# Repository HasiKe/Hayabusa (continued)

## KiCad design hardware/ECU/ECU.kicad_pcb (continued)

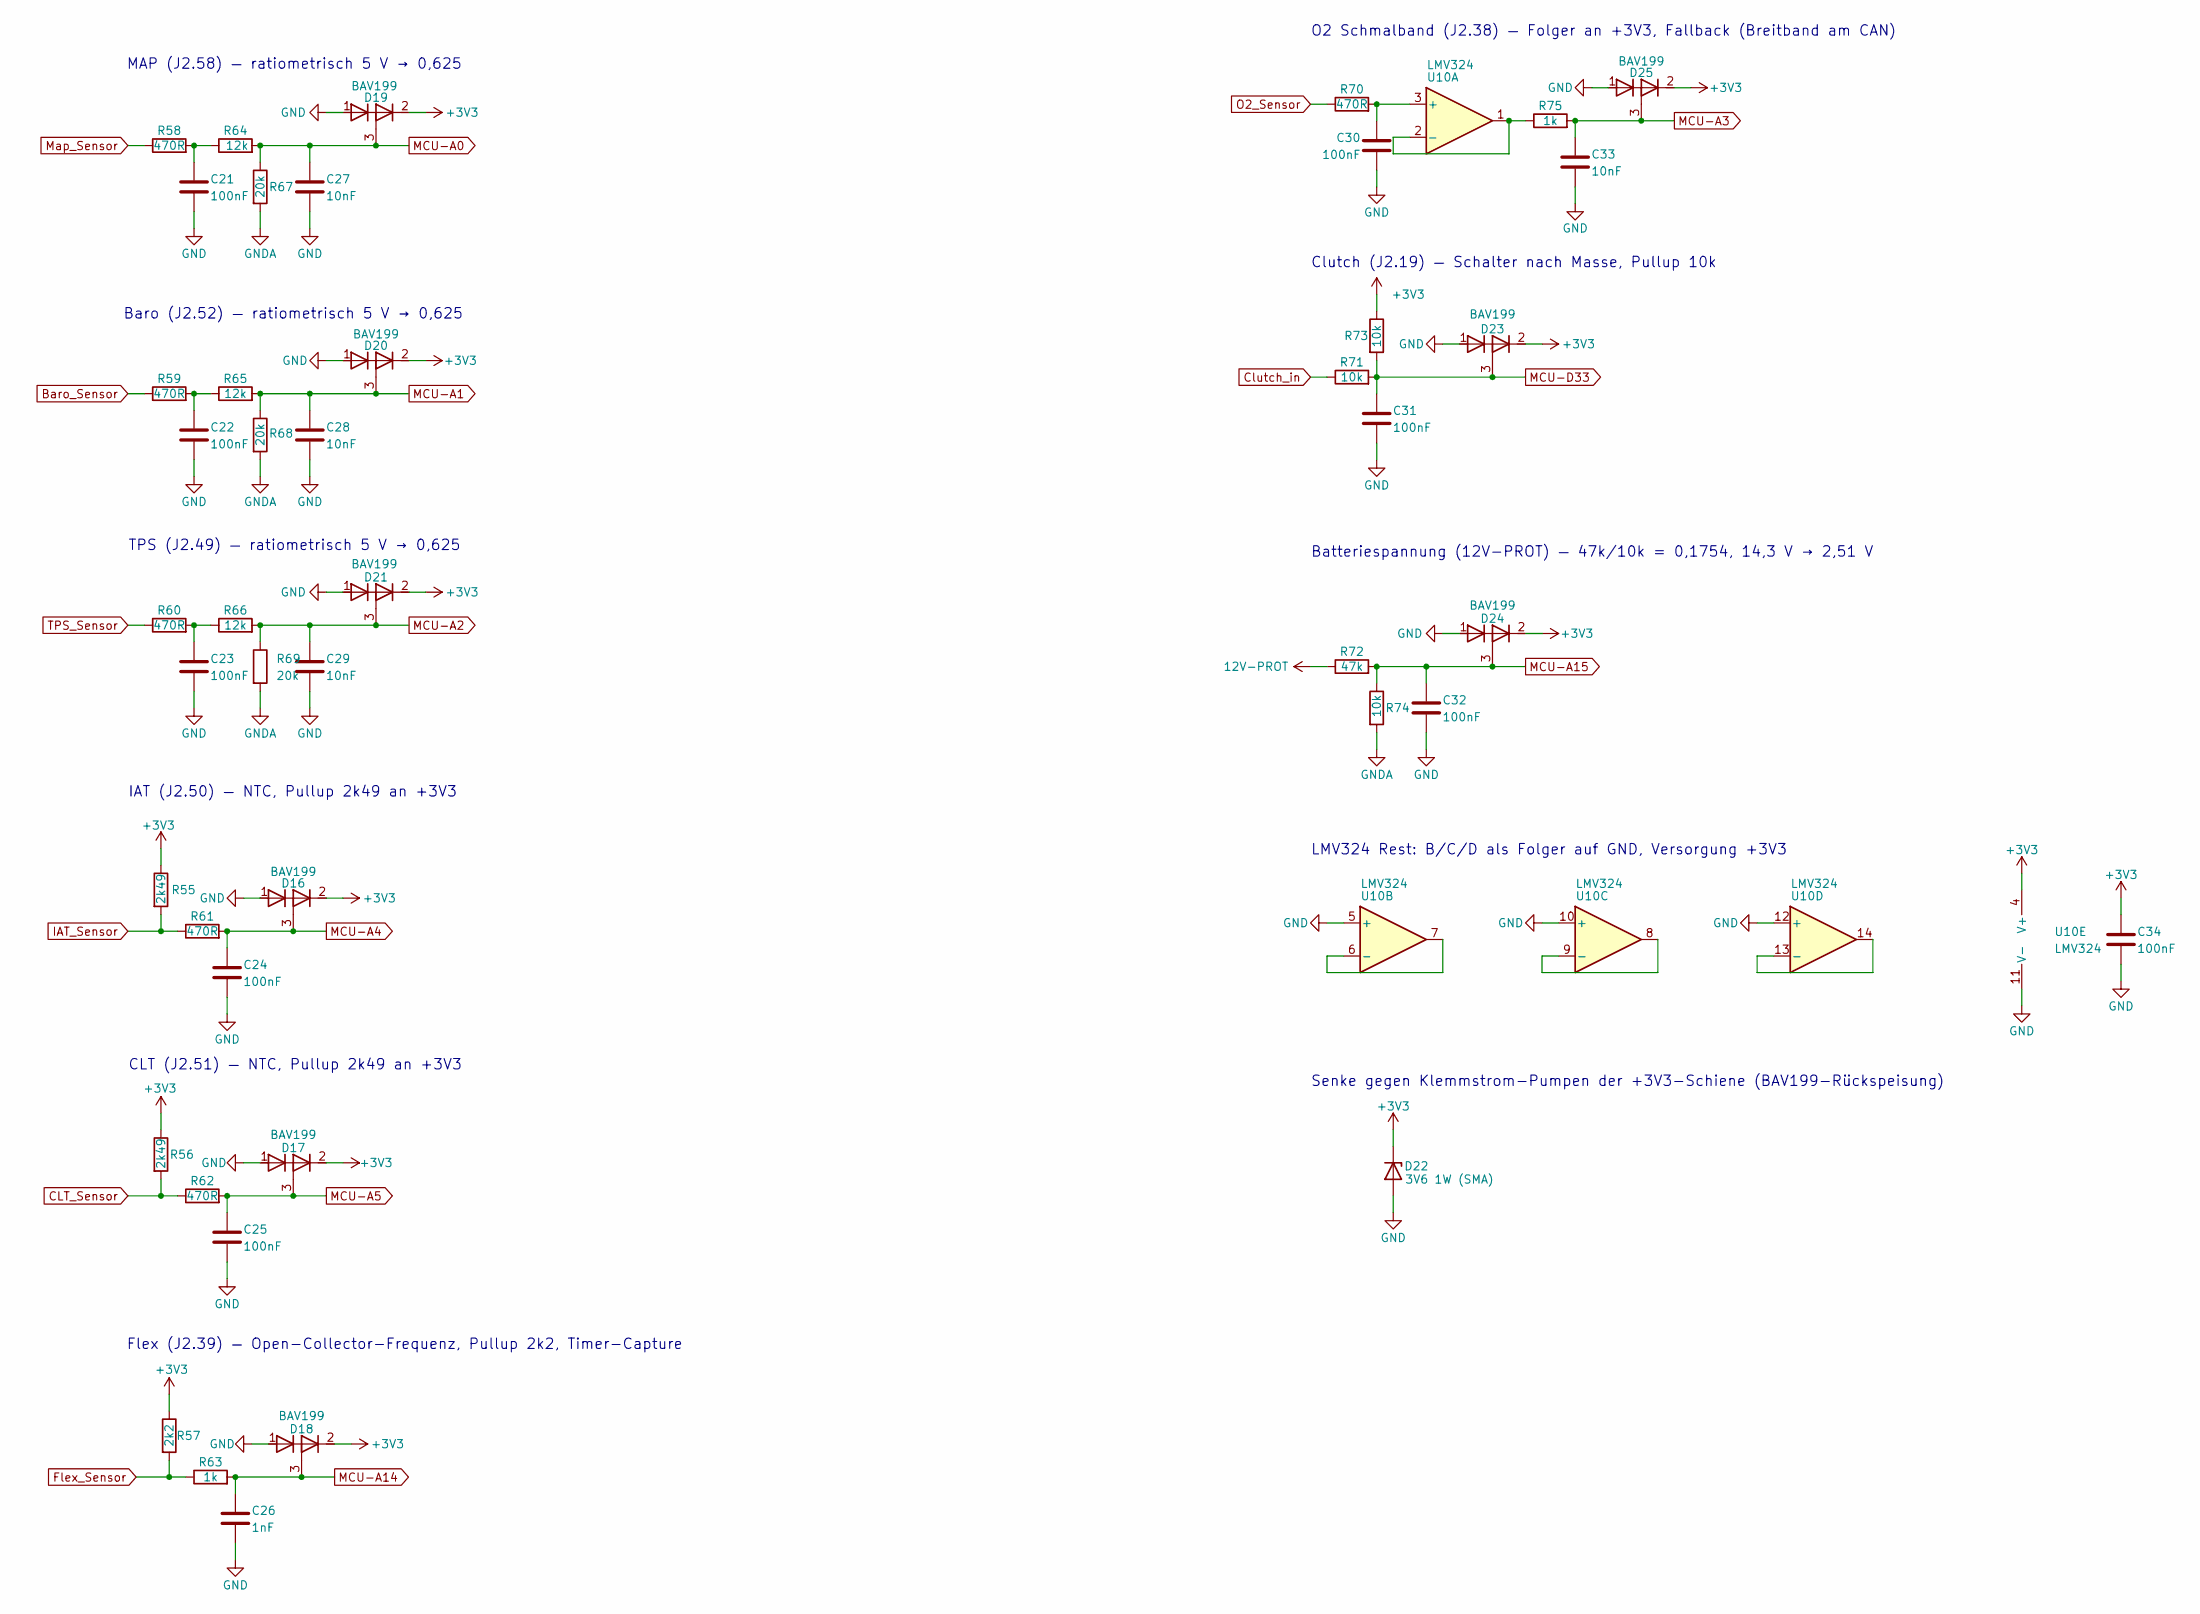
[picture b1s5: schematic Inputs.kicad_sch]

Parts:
C21, C22, C23, C24, C25, C30, C31, C32, C34: 100nF; C_0805_2012Metric; Manufacturer_Part_Number CC0805KRX7R9BB104; Digikey Part Number 311-1140-1-ND
C26: 1nF; C_0805_2012Metric; Manufacturer_Part_Number C0805C102J5HACAUTO; Digikey Part Number 399-16591-1-ND
C27, C28, C29, C33: 10nF; C_0805_2012Metric; Manufacturer_Part_Number CC0805KRX7R9BB103; Digikey Part Number 311-1136-1-ND
D16, D17, D18, D19, D20, D21, D23, D24, D25: BAV199; SOT-23; Manufacturer_Part_Number BAV199LT1G; Digikey Part Number BAV199LT1GOSCT-ND
D22: 3V6 1W (SMA); D_SMA; Manufacturer_Part_Number 1SMA5914BT3G; Digikey Part Number 1SMA5914BT3GOSCT-ND
R55, R56: 2k49; R_0805_2012Metric; Manufacturer_Part_Number RC0805FR-072K49L; Digikey Part Number 311-2.49KCRCT-ND
R57: 2k2; R_0805_2012Metric; Manufacturer_Part_Number RC0805FR-072K2L; Digikey Part Number 311-2.20KCRCT-ND
R58, R59, R60, R61, R62, R70: 470R; R_0805_2012Metric; Manufacturer_Part_Number RC0805FR-07470RL; Digikey Part Number 311-470CRCT-ND
R63, R75: 1k; R_0805_2012Metric; Manufacturer_Part_Number RC0805FR-071KL; Digikey Part Number 311-1.00KCRCT-ND
R64, R65, R66: 12k; R_0805_2012Metric; Manufacturer_Part_Number RC0805FR-0712KL; Digikey Part Number 311-12.0KCRCT-ND
R67, R68, R69: 20k; R_0805_2012Metric; Manufacturer_Part_Number RC0805FR-0720KL; Digikey Part Number 311-20.0KCRCT-ND
R71, R73, R74: 10k; R_0805_2012Metric; Manufacturer_Part_Number RC0805FR-0710KL; Digikey Part Number 311-10.0KCRCT-ND
R72: 47k; R_0805_2012Metric; Manufacturer_Part_Number RC0805FR-0747KL; Digikey Part Number 311-47.0KCRCT-ND
U10: LMV324; SOIC-14_3.9x8.7mm_P1.27mm; Manufacturer_Part_Number LMV324IDR; Digikey Part Number 296-9569-1-ND

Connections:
12V-PROT: R72.1; also elsewhere on the board
+3V3: C34.1, D16.2 (K2), D17.2 (K2), D18.2 (K2), D19.2 (K2), D20.2 (K2), D21.2 (K2), D22.1 (K), D23.2 (K2), D24.2 (K2), D25.2 (K2), R55.1, R56.1, R57.1, R73.1, U10.4 (V+); also elsewhere on the board
Baro_Sensor: R59.1; also elsewhere on the board
CLT_Sensor: R56.2, R62.1; also elsewhere on the board
Clutch_in: R71.1; also elsewhere on the board
Flex_Sensor: R57.2, R63.1; also elsewhere on the board
GND: C21.2, C22.2, C23.2, C24.2, C25.2, C26.2, C27.2, C28.2, C29.2, C30.2, C31.2, C32.2, C33.2, C34.2, D16.1 (A1), D17.1 (A1), D18.1 (A1), D19.1 (A1), D20.1 (A1), D21.1 (A1), D22.2 (A), D23.1 (A1), D24.1 (A1), D25.1 (A1), U10.5 (+), U10.10 (+), U10.11 (V-), U10.12 (+); also elsewhere on the board
GNDA: R67.2, R68.2, R69.2, R74.2; also elsewhere on the board
IAT_Sensor: R55.2, R61.1; also elsewhere on the board
MCU-A0: C27.1, D19.3 (K1A2), R64.2, R67.1; also elsewhere on the board
MCU-A1: C28.1, D20.3 (K1A2), R65.2, R68.1; also elsewhere on the board
MCU-A2: C29.1, D21.3 (K1A2), R66.2, R69.1; also elsewhere on the board
MCU-A3: C33.1, D25.3 (K1A2), R75.2; also elsewhere on the board
MCU-A4: C24.1, D16.3 (K1A2), R61.2; also elsewhere on the board
MCU-A5: C25.1, D17.3 (K1A2), R62.2; also elsewhere on the board
MCU-A14: C26.1, D18.3 (K1A2), R63.2; also elsewhere on the board
MCU-A15: C32.1, D24.3 (K1A2), R72.2, R74.1; also elsewhere on the board
MCU-D33: C31.1, D23.3 (K1A2), R71.2, R73.2; also elsewhere on the board
Map_Sensor: R58.1; also elsewhere on the board
unnamed: C21.1, R58.2, R64.1
unnamed: C22.1, R59.2, R65.1
unnamed: C23.1, R60.2, R66.1
unnamed: C30.1, R70.2, U10.3 (+)
unnamed: R75.1, U10.1, U10.2 (-)
unnamed: U10.6 (-), U10.7
unnamed: U10.8, U10.9 (-)
unnamed: U10.13 (-), U10.14
O2_Sensor: R70.1; also elsewhere on the board
TPS_Sensor: R60.1; also elsewhere on the board

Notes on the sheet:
Senke gegen Klemmstrom-Pumpen der +3V3-Schiene (BAV199-Rückspeisung)
Flex (J2.39) — Open-Collector-Frequenz, Pullup 2k2, Timer-Capture
Baro (J2.52) — ratiometrisch 5 V → 0,625
LMV324 Rest: B/C/D als Folger auf GND, Versorgung +3V3
O2 Schmalband (J2.38) — Folger an +3V3, Fallback (Breitband am CAN)
MAP (J2.58) — ratiometrisch 5 V → 0,625
Batteriespannung (12V-PROT) — 47k/10k = 0,1754, 14,3 V → 2,51 V
TPS (J2.49) — ratiometrisch 5 V → 0,625
Clutch (J2.19) — Schalter nach Masse, Pullup 10k
IAT (J2.50) — NTC, Pullup 2k49 an +3V3
CLT (J2.51) — NTC, Pullup 2k49 an +3V3

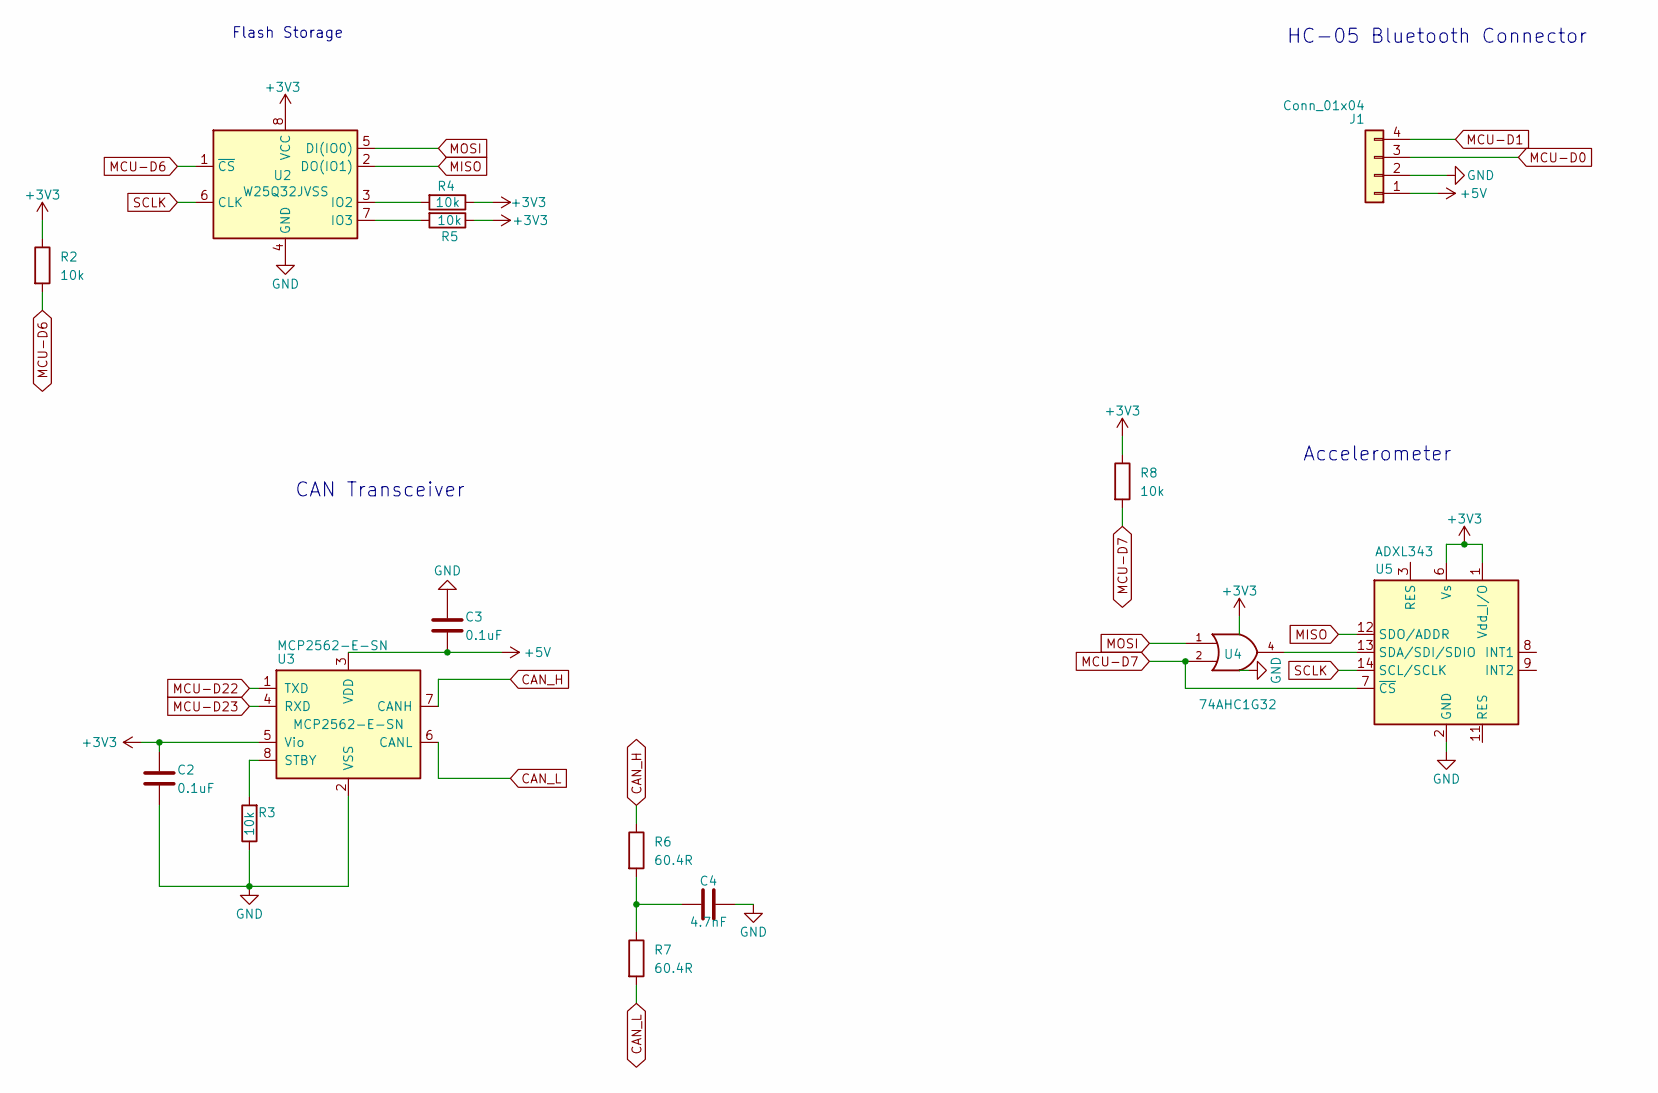
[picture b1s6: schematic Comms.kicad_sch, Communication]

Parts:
C2, C3: 0.1uF; C_0805_2012Metric; Manufacturer_Part_Number CC0805KRX7R9BB104; Digikey Part Number 311-1140-1-ND
C4: 4.7nF; C_0805_2012Metric; Manufacturer_Part_Number CC0805KRX7R9BB472; Digikey Part Number 311-1133-1-ND
J1: Conn_01x04; PinHeader_1x04_P2.54mm_Vertical; Manufacturer_Part_Number 61300411121; Digikey Part Number 732-5317-ND
R2, R3, R4, R5, R8: 10k; R_0805_2012Metric; Manufacturer_Part_Number RC0805FR-0710KL; Digikey Part Number 311-10.0KCRCT-ND
R6, R7: 60.4R; R_0805_2012Metric; Manufacturer_Part_Number RC0805FR-0760R4L; Digikey Part Number 311-60.4CRCT-ND
U2: W25Q32JVSS; SOIC-8_5.3x5.3mm_P1.27mm; Manufacturer_Part_Number W25Q32RVCSJQ TR; Digikey Part Number 256-W25Q32RVCSJQTR-ND
U3: MCP2562-E-SN; SOIC-8_3.9x4.9mm_P1.27mm; Manufacturer_Part_Number MCP2562-E/SN; Digikey Part Number MCP2562-E/SN-ND
U4: 74AHC1G32; SOT-353_SC-70-5; Manufacturer_Part_Number SN74AHC1G32DCKR; Digikey Part Number 296-8749-1-ND
U5: ADXL343; LGA-14_3x5mm_P0.8mm_LayoutBorder1x6y; Manufacturer_Part_Number ADXL343BCCZ-RL; Digikey Part Number ADXL343BCCZ-RLCT-ND

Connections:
+3V3: C2.1, R2.1, R4.1, R5.1, R8.1, U2.8 (VCC), U3.5 (Vio), U4.5 (VCC), U5.1 (Vdd_I/O), U5.6 (Vs); also elsewhere on the board
+5V: C3.2, J1.1, U3.3 (VDD); also elsewhere on the board
CAN_H: R6.1, U3.7 (CANH); also elsewhere on the board
CAN_L: R7.2, U3.6 (CANL); also elsewhere on the board
GND: C2.2, C3.1, C4.2, J1.2, R3.1, U2.4 (GND), U3.2 (VSS), U4.3 (GND), U5.2 (GND), U5.4 (GND), U5.5 (GND); also elsewhere on the board
MCU-D0: J1.3; also elsewhere on the board
MCU-D1: J1.4; also elsewhere on the board
MCU-D6: R2.2, U2.1 (~CS); also elsewhere on the board
MCU-D7: R8.2, U4.2, U5.7 (~CS); also elsewhere on the board
MCU-D22: U3.1 (TXD); also elsewhere on the board
MCU-D23: U3.4 (RXD); also elsewhere on the board
MISO: U2.2 (DO(IO1)), U5.12 (SDO/ADDR); also elsewhere on the board
MOSI: U2.5 (DI(IO0)), U4.1; also elsewhere on the board
unnamed: C4.1, R6.2, R7.1
unnamed: R4.2, U2.3 (IO2)
unnamed: R5.2, U2.7 (IO3)
unnamed: R3.2, U3.8 (STBY)
unnamed: U4.4, U5.13 (SDA/SDI/SDIO)
SCLK: U2.6 (CLK), U5.14 (SCL/SCLK); also elsewhere on the board

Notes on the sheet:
Flash Storage
CAN Transceiver
HC-05 Bluetooth Connector
Accelerometer

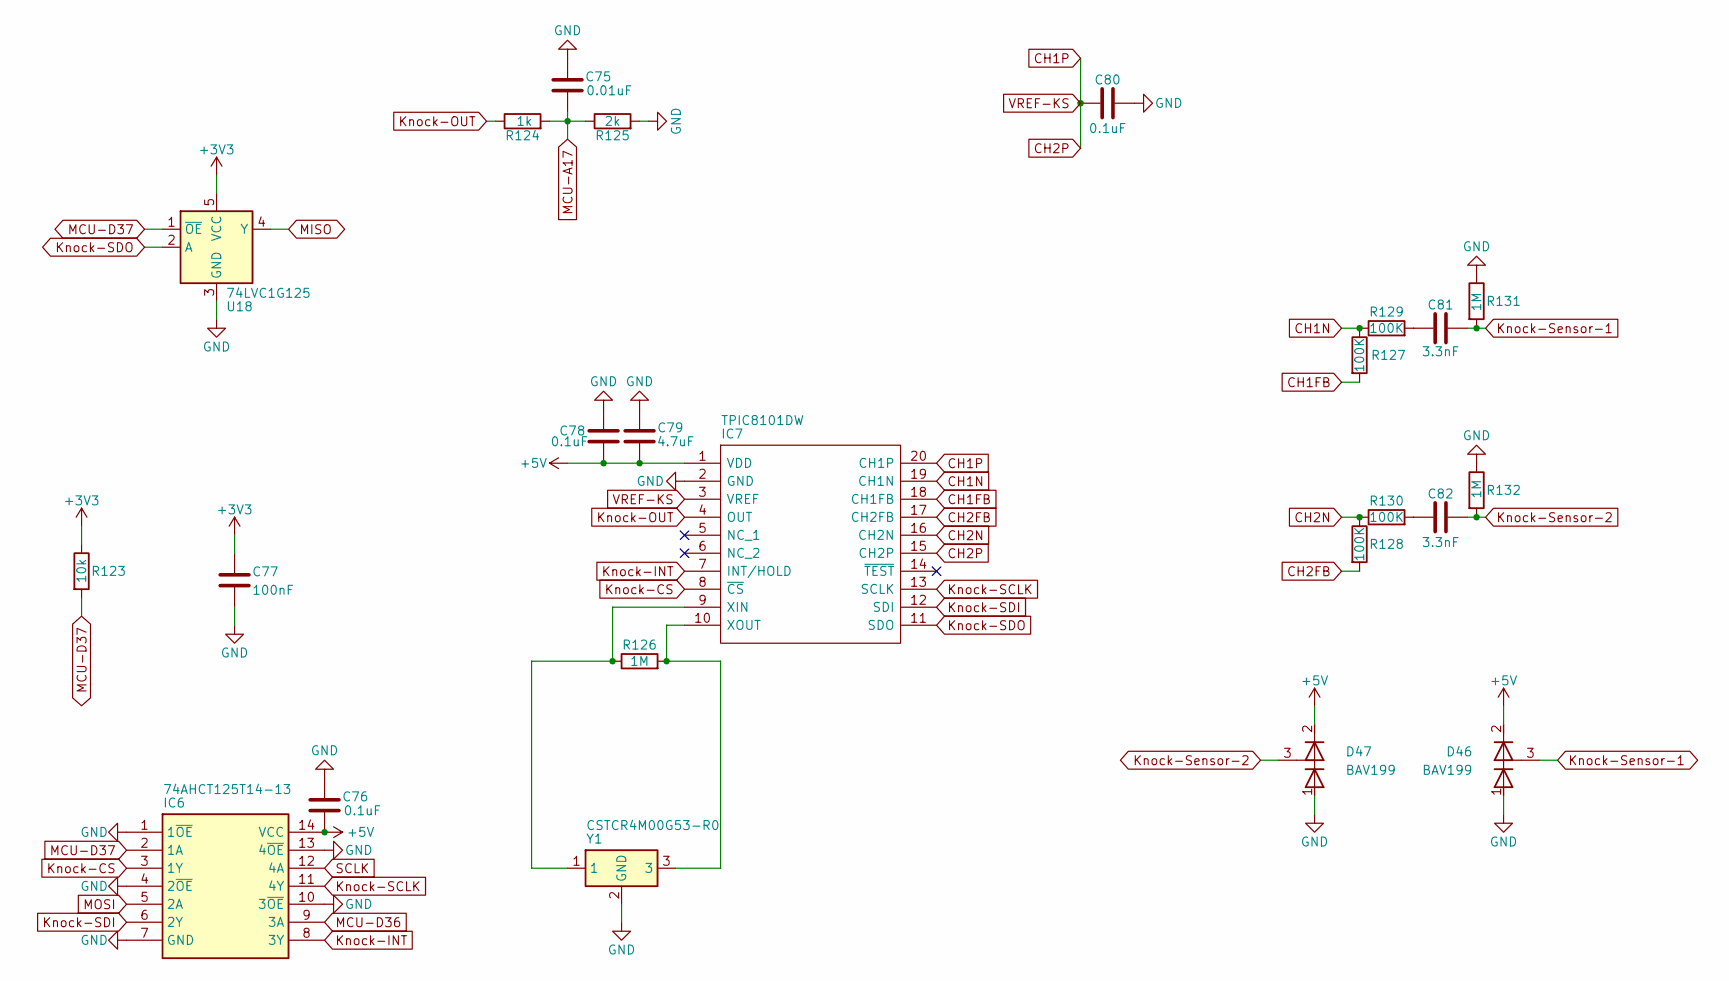
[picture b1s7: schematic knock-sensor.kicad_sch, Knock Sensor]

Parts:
C75: 0.01uF; C_0805_2012Metric; Manufacturer_Part_Number CC0805KRX7R9BB103; Digikey Part Number 311-1136-1-ND
C76, C78, C80: CC0805KRX7R9BB104; C_0805_2012Metric; Mouser Part Number 603-CC805KRX7R9BB104
C77: 100nF; C_0805_2012Metric; Manufacturer_Part_Number CC0805KRX7R9BB104; Digikey Part Number 311-1140-1-ND
C79: CC0805KKX7R7BB475; C_0805_2012Metric; Mouser Part Number 603-CC805KKX7R7BB475
C81, C82: CC0805JRX7R9BB332; C_0805_2012Metric; Manufacturer_Part_Number CC0805JRX7R9BB332; Digikey Part Number 311-4277-1-ND
D46, D47: BAV199; SOT-23; Manufacturer_Part_Number BAV199LT1G; Digikey Part Number BAV199LT1GOSCT-ND
IC6: 74AHCT125T14-13; TSSOP-14_4.4x5mm_P0.65mm; Manufacturer_Part_Number 74AHCT125T14-13; Mouser Part Number 621-74AHCT125T14-13
IC7: TPIC8101DW; SOIC-20W_7.5x12.8mm_P1.27mm; Manufacturer_Part_Number TPIC8101DWR; Mouser Part Number 595-TPIC8101DW
R123: 10k; R_0805_2012Metric; Manufacturer_Part_Number RC0805FR-0710KL; Digikey Part Number 311-10.0KCRCT-ND
R124: 1k; R_0805_2012Metric; Manufacturer_Part_Number RC0805FR-071KL; Digikey Part Number 311-1.00KCRCT-ND
R125: 2k; R_0805_2012Metric; Manufacturer_Part_Number RC0805FR-072KL; Mouser Part Number 603-RC0805FR-072KL
R126, R131, R132: RC0805FR-071ML; R_0805_2012Metric; Mouser Part Number 603-RC0805FR-071ML
R127, R128, R129, R130: RC0805FR-07100KL; R_0805_2012Metric; Mouser Part Number 603-RC0805FR-07100KL
U18: 74LVC1G125; SOT-353_SC-70-5; Manufacturer_Part_Number SN74LVC1G125DCKR; Digikey Part Number 296-11604-1-ND
Y1: CSTCR4M00G53-R0; Resonator_SMD_Murata_CSTCR_4.5x2x1.15mm; Manufacturer_Part_Number CSTCR4M00G53-R0; Digikey Part Number 490-1200-1-ND

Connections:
+3V3: C77.1, R123.1, U18.5 (VCC); also elsewhere on the board
+5V: C76.2, C78.2, C79.2, D46.2 (K2), D47.2 (K2), IC6.14 (VCC), IC7.1 (VDD); also elsewhere on the board
CH1FB: IC7.18 (CH1FB), R127.2
CH1N: IC7.19 (CH1N), R127.1, R129.1
CH1P: C80.1, IC7.3 (VREF), IC7.15 (CH2P), IC7.20 (CH1P)
CH2FB: IC7.17 (CH2FB), R128.2
CH2N: IC7.16 (CH2N), R128.1, R130.1
GND: C75.1, C76.1, C77.2, C78.1, C79.1, C80.2, D46.1 (A1), D47.1 (A1), IC6.1 (1~OE), IC6.4 (2~OE), IC6.7 (GND), IC6.10 (3~OE), IC6.13 (4~OE), IC7.2 (GND), R125.2, R131.1, R132.1, U18.3 (GND), Y1.2 (GND); also elsewhere on the board
Knock-CS: IC6.3 (1Y), IC7.8 (~CS)
Knock-INT: IC6.8 (3Y), IC7.7 (INT/HOLD)
Knock-OUT: IC7.4 (OUT), R124.1
Knock-SCLK: IC6.11 (4Y), IC7.13 (SCLK)
Knock-SDI: IC6.6 (2Y), IC7.12 (SDI)
Knock-SDO: IC7.11 (SDO), U18.2 (A)
Knock-Sensor-1: C81.2, D46.3 (K1A2), R131.2; also elsewhere on the board
Knock-Sensor-2: C82.2, D47.3 (K1A2), R132.2; also elsewhere on the board
MCU-A17: C75.2, R124.2, R125.1; also elsewhere on the board
MCU-D36: IC6.9 (3A); also elsewhere on the board
MCU-D37: IC6.2 (1A), R123.2, U18.1 (~OE); also elsewhere on the board
MISO: U18.4 (Y); also elsewhere on the board
MOSI: IC6.5 (2A); also elsewhere on the board
unnamed: C81.1, R129.2
unnamed: C82.1, R130.2
unnamed: IC7.9 (XIN), R126.1, Y1.1
unnamed: IC7.10 (XOUT), R126.2, Y1.3
SCLK: IC6.12 (4A); also elsewhere on the board

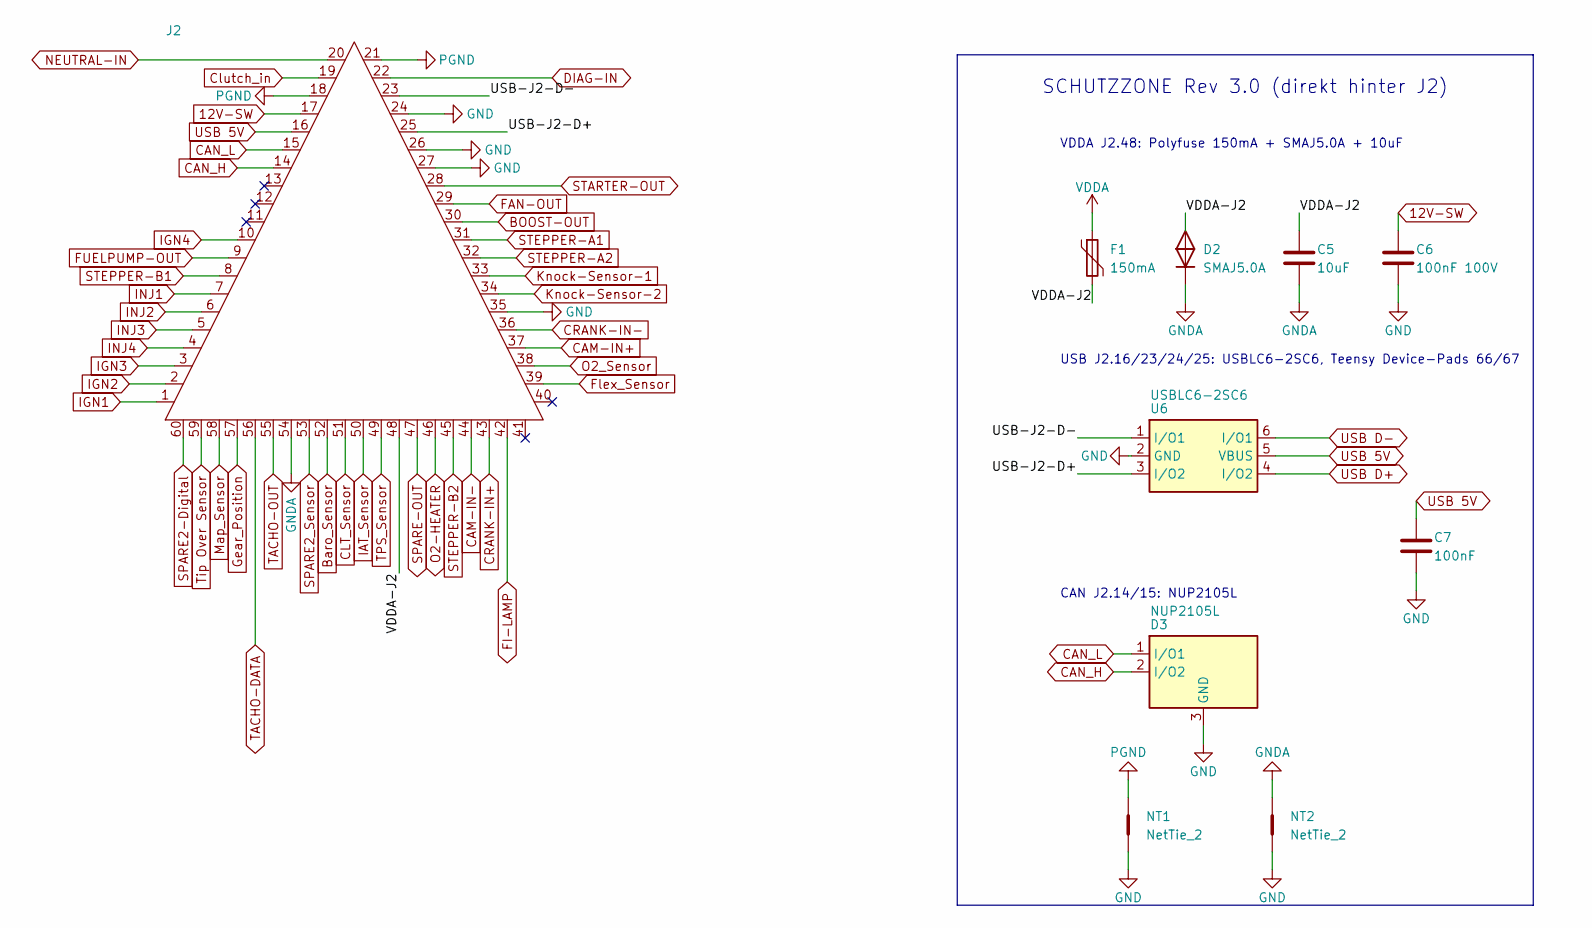
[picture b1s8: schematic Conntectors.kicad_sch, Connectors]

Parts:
C5: 10uF; C_1206_3216Metric; Manufacturer_Part_Number GRM31CR71E106KA12L; Digikey Part Number 490-6518-1-ND
C6: 100nF 100V; C_1206_3216Metric; Manufacturer_Part_Number C1206C104K1RACTU; Digikey Part Number 399-C1206C104K1RACTUCT-ND
C7: 100nF; C_0805_2012Metric; Manufacturer_Part_Number CC0805KRX7R9BB104; Digikey Part Number 311-1140-1-ND
D2: SMAJ5.0A; D_SMA; Manufacturer_Part_Number SMAJ5.0A; Digikey Part Number SMAJ5.0ALFCT-ND
D3: NUP2105L; SOT-23; Manufacturer_Part_Number NUP2105LT1G; Digikey Part Number NUP2105LT1GOSCT-ND
F1: 150mA; Fuse_1812_4532Metric; Manufacturer_Part_Number 1812L014DR; Digikey Part Number F3353CT-ND
J2: 6437288-3; Manufacturer_Part_Number 6437288-3; Digikey Part Number A122211-ND
NT1, NT2: NetTie_2; NetTie-2_SMD_Pad0.5mm
U6: USBLC6-2SC6; SOT-23-6; Manufacturer_Part_Number USBLC6-2SC6; Digikey Part Number 497-5235-1-ND

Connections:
12V-SW: C6.1, J2.17; also elsewhere on the board
/Conntectors/USB-J2-D+: J2.25, U6.3 (I/O2)
/Conntectors/USB-J2-D-: J2.23, U6.1 (I/O1)
/Conntectors/VDDA-J2: C5.1, D2.1, F1.2, J2.48
BOOST-OUT: J2.30; also elsewhere on the board
Baro_Sensor: J2.52; also elsewhere on the board
CAM-IN+: J2.37; also elsewhere on the board
CAM-IN-: J2.44; also elsewhere on the board
CAN_H: D3.2 (I/O2), J2.14; also elsewhere on the board
CAN_L: D3.1 (I/O1), J2.15; also elsewhere on the board
CLT_Sensor: J2.51; also elsewhere on the board
CRANK-IN+: J2.43; also elsewhere on the board
CRANK-IN-: J2.36; also elsewhere on the board
Clutch_in: J2.19; also elsewhere on the board
DIAG-IN: J2.22
FAN-OUT: J2.29; also elsewhere on the board
FI-LAMP: J2.42; also elsewhere on the board
FUELPUMP-OUT: J2.9; also elsewhere on the board
Flex_Sensor: J2.39; also elsewhere on the board
GND: C6.2, C7.2, D3.3 (GND), J2.24, J2.26, J2.27, J2.35, NT1.2, NT2.2, U6.2 (GND); also elsewhere on the board
GNDA: C5.2, D2.2, J2.54, NT2.1; also elsewhere on the board
Gear_Position: J2.57; also elsewhere on the board
IAT_Sensor: J2.50; also elsewhere on the board
IGN1: J2.1; also elsewhere on the board
IGN2: J2.2; also elsewhere on the board
IGN3: J2.3; also elsewhere on the board
IGN4: J2.10; also elsewhere on the board
INJ1: J2.7; also elsewhere on the board
INJ2: J2.6; also elsewhere on the board
INJ3: J2.5; also elsewhere on the board
INJ4: J2.4; also elsewhere on the board
Knock-Sensor-1: J2.33; also elsewhere on the board
Knock-Sensor-2: J2.34; also elsewhere on the board
Map_Sensor: J2.58; also elsewhere on the board
NEUTRAL-IN: J2.20; also elsewhere on the board
O2-HEATER: J2.46; also elsewhere on the board
O2_Sensor: J2.38; also elsewhere on the board
PGND: J2.18, J2.21, NT1.1; also elsewhere on the board
SPARE2-Digital: J2.60; also elsewhere on the board
SPARE2_Sensor: J2.53; also elsewhere on the board
SPARE-OUT: J2.47; also elsewhere on the board
STARTER-OUT: J2.28; also elsewhere on the board
STEPPER-A1: J2.31; also elsewhere on the board
STEPPER-A2: J2.32; also elsewhere on the board
STEPPER-B1: J2.8; also elsewhere on the board
STEPPER-B2: J2.45; also elsewhere on the board
TACHO-DATA: J2.56
TACHO-OUT: J2.55; also elsewhere on the board
TPS_Sensor: J2.49; also elsewhere on the board
Tip Over Sensor: J2.59; also elsewhere on the board
USB 5V: C7.1, J2.16, U6.5 (VBUS)
USB D+: U6.4 (I/O2); also elsewhere on the board
USB D-: U6.6 (I/O1); also elsewhere on the board
VDDA: F1.1; also elsewhere on the board

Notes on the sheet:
SCHUTZZONE Rev 3.0 (direkt hinter J2)
VDDA J2.48: Polyfuse 150mA + SMAJ5.0A + 10uF
USB J2.16/23/24/25: USBLC6-2SC6, Teensy Device-Pads 66/67
CAN J2.14/15: NUP2105L

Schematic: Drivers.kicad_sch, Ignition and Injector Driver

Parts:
C15, C17: 0.1uF; C_0805_2012Metric; Manufacturer_Part_Number CC0805KRX7R9BB104; Digikey Part Number 311-1140-1-ND
C16, C18: 33uF; CP_Elec_6.3x7.7; Voltage 50V; Manufacturer_Part_Number EEE-1HA330XP; Digikey Part Number PCE3925CT-ND
C19, C20: 100n; C_0805_2012Metric; Manufacturer_Part_Number CC0805KRX7R9BB104; Digikey Part Number 311-1140-1-ND
D8, D9, D14, D15: LED; LED_0805_2012Metric; Manufacturer_Part_Number LTST-C170KRKT; Digikey Part Number 160-1415-1-ND
D10, D11, D12, D13: D; D_SOD-323; Manufacturer_Part_Number 1N4448WX-TP; Digikey Part Number 1N4448WXTPMSCT-ND
Q1, Q2, Q3, Q4: ISL9V5036P3-F085; TO254P470X1016X2019-3P; Manufacturer_Part_Number ISL9V5036P3-F085; Mouser Part Number 512-ISL9V5036P3-F085
R27, R31, R32, R33, R34, R35: 10k; R_0805_2012Metric; Manufacturer_Part_Number RC0805FR-0710KL; Digikey Part Number 311-10.0KCRCT-ND
R28, R29, R53, R54: 33; R_0805_2012Metric; Manufacturer_Part_Number RC0805FR-7W33RL; Digikey Part Number 13-RC0805FR-7W33RLCT-ND
R30: 20m; R_2512_6332Metric; Manufacturer_Part_Number WSL2512R0200FEA; Digikey Part Number WSLG-.02CT-ND
R36, R37, R38, R39, R42, R43, R44, R45: 18k; R_1206_3216Metric; Manufacturer_Part_Number RC1206FR-0718KL; Digikey Part Number 311-18.0KFRCT-ND
R40, R41, R51, R52: 1k; R_0805_2012Metric; Manufacturer_Part_Number RC0805FR-071KL; Digikey Part Number 311-1.00KCRCT-ND
R46, R47, R48, R49: 4.02k; R_0805_2012Metric; Manufacturer_Part_Number RC0805FR-074K02L; Digikey Part Number 311-4.02KCRCT-ND
R50: 100k; R_0805_2012Metric; Manufacturer_Part_Number RC0805FR-07100KL; Digikey Part Number 311-100KCRCT-ND
U7: MC33810; SOIC32-P0.65-33N; Manufacturer_Part_Number MCZ33810EK; Digikey Part Number MCZ33810EK-ND
U8: TPS3823-33DBV; SOT-23-5; Manufacturer_Part_Number TPS3823-33DBVR; Digikey Part Number 296-1357-1-ND
U9: 74LVC1G00; SOT-353_SC-70-5; Manufacturer_Part_Number SN74LVC1G00DCKR; Digikey Part Number 296-9846-1-ND

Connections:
12V-PROT: C17.1, C18.1, R40.2, R41.1, R51.2, R52.2, U7.25 (VPWR); also elsewhere on the board
+3V3: C15.2, C16.1, C19.1, C20.1, R27.2, R35.2, U7.8 (VDD), U8.3 (~MR), U8.5 (VDD), U9.5 (VCC); also elsewhere on the board
/Drivers/FB0: R42.2, R46.1, U7.2 (FB0)
/Drivers/FB1: R43.2, R47.1, U7.15 (FB1)
/Drivers/FB2: R44.2, R48.1, U7.31 (FB2)
/Drivers/FB3: R45.2, R49.1, U7.18 (FB3)
/Drivers/G_IGN1: Q2.1, R29.1, R31.1
/Drivers/G_IGN2: Q1.1, R28.1, R32.1
/Drivers/G_IGN3: Q3.1, R33.1, R53.1
/Drivers/G_IGN4: Q4.1, R34.1, R54.1
/Drivers/IGBT_E: Q1.3, Q2.3, Q3.3, Q4.3, R30.1, R31.2, R32.2, R33.2, R34.2, U7.26 (RSP)
/Drivers/WDT-RESET: U8.1 (~RESET), U9.2 (B)
GND: C15.1, C16.2, C17.2, C18.2, C19.2, C20.2, R50.2, U8.2 (GND), U9.3 (GND); also elsewhere on the board
IGN1: Q2.2, R36.1; also elsewhere on the board
IGN2: Q1.2, R37.1; also elsewhere on the board
IGN3: Q3.2, R38.1; also elsewhere on the board
IGN4: Q4.2, R39.1; also elsewhere on the board
INJ1: D11.1 (K), U7.1 (OUT0); also elsewhere on the board
INJ2: D10.1 (K), U7.16 (OUT1); also elsewhere on the board
INJ3: D13.1 (K), U7.32 (OUT2); also elsewhere on the board
INJ4: D12.1 (K), U7.17 (OUT3); also elsewhere on the board
MC33810_1-CS: R27.1, U7.4 (CS); also elsewhere on the board
MCU-D2: R50.1, U9.1 (A); also elsewhere on the board
MCU-D3: U8.4 (WDI); also elsewhere on the board
MISO: U7.7 (SO); also elsewhere on the board
MOSI: U7.6 (SI); also elsewhere on the board
unnamed: D8.2 (A), R40.1
unnamed: D9.2 (A), R41.2
unnamed: D8.1 (K), D10.2 (A)
unnamed: D9.1 (K), D11.2 (A)
unnamed: D12.2 (A), D14.1 (K)
unnamed: D13.2 (A), D15.1 (K)
unnamed: D14.2 (A), R51.1
unnamed: D15.2 (A), R52.1
unnamed: R36.2, R42.1
unnamed: R37.2, R43.1
unnamed: R38.2, R44.1
unnamed: R39.2, R45.1
OUTEN_1: R35.1, U7.9 (OUTEN), U9.4 (Y)
PGND: R30.2, R46.2, R47.2, R48.2, R49.2, U7.27 (RSN), U7.33 (GND); also elsewhere on the board
SCLK: U7.5 (SCLK); also elsewhere on the board
T_IGN1: R29.2, U7.3 (GD0)
T_IGN2: R28.2, U7.14 (GD1)
T_IGN3: R53.2, U7.30 (GD2)
T_IGN4: R54.2, U7.19 (GD3)

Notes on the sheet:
Zuendstrom-Shunt: alle IGBT-Emitter -> 20mOhm -> PGND
OUTEN-Safety: OUTEN aktiv LOW, R16 Pull-Up +3V3 (Boot=AUS).
RSP=IGBT_E, RSN=PGND (Kelvin-Layout!), Schwellen per SPI-DAC, Gain=2
Brownout/MCU-Absturz -> RESET low -> NAND=HIGH -> alle 8 Endstufen aus.
TC4424/SW3/F1/IGN_V+ entfallen. VPWR/Freilauf an 12V-PROT. U7-GND = PGND (Injektor-Rueckstrom).
Rev 3.0: MC33810 GD0-3 (5-9V Ladungspumpe) -> 33R -> ISL9V5036 direkt.
Freigabe nur bei MCU-D2=HIGH UND Watchdog-RESET=HIGH (WDI<1.6s von MCU-D3).
*Note: Max current per injector channel is 3.5A

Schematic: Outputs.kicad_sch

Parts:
C44, C45: 10n; C_0805_2012Metric; Manufacturer_Part_Number CC0805KRX7R9BB103; Digikey Part Number 311-1136-1-ND
C46: 100u/50V; CP_Elec_8x10; Manufacturer_Part_Number EEE-FK1H101GP; Digikey Part Number PCE4323CT-ND
C47: 1u; C_0805_2012Metric; Manufacturer_Part_Number CC0805KKX7R7BB105; Digikey Part Number 311-1365-1-ND
C48: 220n; C_0805_2012Metric; Manufacturer_Part_Number CC0805KKX7R9BB224; Digikey Part Number 311-1887-1-ND
C49: 22n; C_0805_2012Metric; Manufacturer_Part_Number CC0805KRX7R9BB223; Digikey Part Number 311-1138-1-ND
C50: 1n; C_0805_2012Metric; Manufacturer_Part_Number C0805C102J5HACAUTO; Digikey Part Number 399-16591-1-ND
C51, C52: 100n; C_0805_2012Metric; Manufacturer_Part_Number CC0805KRX7R9BB104; Digikey Part Number 311-1140-1-ND
D31, D32, D33, D34, D35, D36, D39, D40: SS34; D_SMA; Manufacturer_Part_Number B340A-13-F; Digikey Part Number B340A-FDICT-ND
D37, D38: 1N4148W; D_SOD-123; Manufacturer_Part_Number 1N4148W-7-F; Digikey Part Number 1N4148W-FDICT-ND
IC2, IC3, IC4: ZXMS6006DT8; SOT153P700X170-8N; Manufacturer_Part_Number ZXMS6006DT8TA; Digikey Part Number ZXMS6006DT8TADICT-ND
Q5: BSS138; SOT-23; Manufacturer_Part_Number BSS138; Digikey Part Number BSS138CT-ND
R93, R94, R95, R96, R97, R98: 1k; R_0805_2012Metric; Manufacturer_Part_Number RC0805FR-071KL; Digikey Part Number 311-1.00KCRCT-ND
R99, R100, R101, R102, R103, R104, R108, R109, R112: 100k; R_0805_2012Metric; Manufacturer_Part_Number RC0805FR-07100KL; Digikey Part Number 311-100KCRCT-ND
R105: 15k; R_0805_2012Metric; Manufacturer_Part_Number RC0805FR-0715KL; Digikey Part Number 311-15.0KCRCT-ND
R106, R110, R111, R113: 10k; R_0805_2012Metric; Manufacturer_Part_Number RC0805FR-0710KL; Digikey Part Number 311-10.0KCRCT-ND
R107: 330k; R_0805_2012Metric; Manufacturer_Part_Number RC0805FR-07330KL; Digikey Part Number 311-330KCRCT-ND
U12: DRV8434A; HTSSOP-28-1EP_4.4x9.7mm_P0.65mm_EP2.85x5.4mm_ThermalVias; Manufacturer_Part_Number DRV8434APWPR; Digikey Part Number 296-DRV8434APWPRCT-ND
U13, U14: BTF3050TE; TO-252-5_TabPin3; Manufacturer_Part_Number BTF3050TEATMA1; Digikey Part Number BTF3050TEATMA1CT-ND

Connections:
12V-PROT: C44.1, C45.1, C46.1, C48.1, D31.1 (K), D32.1 (K), D33.1 (K), D34.1 (K), D35.1 (K), D36.1 (K), D39.1 (K), D40.1 (K), U12.2 (VM), U12.13 (VM); also elsewhere on the board
+3V3: C51.1, C52.1, R113.1, U12.18 (M0), U12.22 (M1), U13.2 (VDD), U14.2 (VDD); also elsewhere on the board
/Outputs/DRV_DVDD: C47.1, R105.1, U12.15 (DVDD)
/Outputs/DRV_STLM: R107.1, U12.21 (STL_MODE)
/Outputs/DRV_TRQ: C50.1, U12.20 (TRQ_CNT/STL_TH)
/Outputs/DRV_VREF: R105.2, R106.1, U12.17 (VREF)
/Outputs/G_FAN: IC4.1 (INPUT_1), R97.2, R103.1
/Outputs/G_FI: IC2.1 (INPUT_1), R93.2, R99.1
/Outputs/G_FUEL: IC3.1 (INPUT_1), R95.2, R101.1
/Outputs/G_SPARE: IC4.3 (INPUT_2), R98.2, R104.1
/Outputs/G_STRT: IC2.3 (INPUT_2), R94.2, R100.1
/Outputs/G_TACH: IC3.3 (INPUT_2), R96.2, R102.1
/Outputs/OUT-FAULT-H: D37.1 (K), D38.1 (K), Q5.1 (G), R112.1
/Outputs/SRP_BOOST: D37.2 (A), R110.1, U13.4 (SRP)
/Outputs/SRP_O2: D38.2 (A), R111.1, U14.4 (SRP)
BOOST-OUT: D39.2 (A), U13.3 (OUT); also elsewhere on the board
FAN-OUT: D35.2 (A), IC4.7 (DRAIN_1_1), IC4.8 (DRAIN_1_2); also elsewhere on the board
FI-LAMP: D31.2 (A), IC2.7 (DRAIN_1_1), IC2.8 (DRAIN_1_2); also elsewhere on the board
FUELPUMP-OUT: D33.2 (A), IC3.7 (DRAIN_1_1), IC3.8 (DRAIN_1_2); also elsewhere on the board
GND: C47.2, C50.2, C51.2, C52.2, Q5.3 (S), R99.2, R100.2, R101.2, R102.2, R103.2, R104.2, R106.2, R107.2, R108.1, R109.1, R110.2, R111.2, R112.2, U12.14 (GND), U12.29 (PAD); also elsewhere on the board
MCU-D5: R95.1; also elsewhere on the board
MCU-D8: R96.1; also elsewhere on the board
MCU-D9: Q5.2 (D), R113.2, U12.16 (nFAULT); also elsewhere on the board
MCU-D24: R108.2, U13.1 (IN); also elsewhere on the board
MCU-D25: R109.2, U14.1 (IN); also elsewhere on the board
MCU-D26: R94.1; also elsewhere on the board
MCU-D27: R93.1; also elsewhere on the board
MCU-D28: R98.1; also elsewhere on the board
MCU-D29: R97.1; also elsewhere on the board
MCU-D30: U12.23 (STEP); also elsewhere on the board
MCU-D31: U12.24 (DIR); also elsewhere on the board
MCU-D32: U12.25 (ENABLE), U12.26 (nSLEEP); also elsewhere on the board
unnamed: C49.2, U12.28 (CPH)
unnamed: C49.1, U12.27 (CPL)
unnamed: C48.2, U12.1 (VCP)
O2-HEATER: D40.2 (A), U14.3 (OUT); also elsewhere on the board
PGND: C44.2, C45.2, C46.2, IC2.2 (SOURCE_1), IC2.4 (SOURCE_2), IC3.2 (SOURCE_1), IC3.4 (SOURCE_2), IC4.2 (SOURCE_1), IC4.4 (SOURCE_2), U12.3 (PGND), U12.12 (PGND), U13.5 (GND), U14.5 (GND); also elsewhere on the board
SPARE-OUT: D36.2 (A), IC4.5 (DRAIN_2_1), IC4.6 (DRAIN_2_2); also elsewhere on the board
STARTER-OUT: D32.2 (A), IC2.5 (DRAIN_2_1), IC2.6 (DRAIN_2_2); also elsewhere on the board
STEPPER-A1: U12.4 (AOUT1), U12.5 (AOUT1); also elsewhere on the board
STEPPER-A2: U12.6 (AOUT2), U12.7 (AOUT2); also elsewhere on the board
STEPPER-B1: U12.10 (BOUT1), U12.11 (BOUT1); also elsewhere on the board
STEPPER-B2: U12.8 (BOUT2), U12.9 (BOUT2); also elsewhere on the board
TACHO-OUT: D34.2 (A), IC3.5 (DRAIN_2_1), IC3.6 (DRAIN_2_2); also elsewhere on the board

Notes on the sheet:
D) Status-ODER: SRP high (Übertemperatur-Latch) → Diode → OUT-FAULT-H → BSS138 zieht MCU-D9 (nFAULT, wired-OR) auf low
C) BTF3050TE Smart-Low-Side (VDD=+3V3 → Status 3V3-sicher; R_SRP 10k = Slew/Status; Freilauf SS34 nach 12V-PROT)
B) ZXMS6006DT8 Dual-Low-Side — IC2: FI-Lampe / Starter-Relais, IC3: Kraftstoffpumpe / Tacho, IC4: Lüfter / Spare
DRV8434A Peripherie
A) Gate-Netzwerke: MCU-Pin → 1k → Gate, 100k Pulldown (Boot-sicher aus)
E) DRV8434A Stepper (VM=12V-PROT, 1/8-Schritt, IFS = VREF/1.32 V/A = 1.0 A @ VREF 1.32 V, Stall-Erkennung aus, nFAULT → MCU-D9)
